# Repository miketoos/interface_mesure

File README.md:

# Projet d'Interface de Mesure pour Calculateur de Voiture

Ce projet vise à développer une interface de mesure entre un calculateur de voiture et l'être humain. L'objectif principal est de gérer jusqu'à 4 signaux d'injection pour une première carte, tandis que pour une deuxième carte, l'interface doit gérer les signaux de PMH (Point Mort Haut), l'écart en degré sur l'avance à l'allumage, le temps de conduction et la valeur d'accélération.

## Configuration du Projet
### Matériel Requis
- Accès à un calculateur de voiture (Clio 2)
- Carte électronique Arduino
- Sonde de programmation JLink
- Port USB B pour le téléversement du code

### Installation des Pilotes
1. Ajoutez la carte via le lien : [https://www.mattairtech.com/software/arduino/package_MattairTech_index.json](https://www.mattairtech.com/software/arduino/package_MattairTech_index.json)
2. Installez la carte via Outils / Type de carte / Gestionnaire de carte
3. Recherchez "MattairTech SAMD|L|C core for Arduino" et installez-le

### Programmation de la Carte
1. Sélectionnez la carte dans Arduino : Outils / Type de carte / "MattairTech MT-D21E(rev B)"
2. Sélectionnez l'oscillateur interne et le port de communication

### Blink (Test de Programmation)
- Assurez-vous que la carte est détectée dans le logiciel Arduino
- Chargez le programme Blink pour tester la programmation

## Fonctionnalités Principales
### Injection
- Contrôle jusqu'à 4 signaux d'injection pour la première carte (à compléter)

### Régime Moteur
- Mesure et affichage du régime moteur en tr/min

### Avance à l'Allumage
- Calcul et contrôle de l'avance à l'allumage en degrés

### Temps de Conduction
- Mesure du temps de conduction du moteur

### Accélération
- Calcul de l'accélération en fonction du régime moteur

## Production et Commande
- Les fichiers Gerber dans la section hardware permettent la production de cartes électroniques. Les entreprises peuvent être contactées en fournissant ces fichiers.
- Les fichiers de la section mécanique facilitent la production de boîtiers pour les cartes électroniques.

## Téléversement du Code
- Les codes nécessaires sont disponibles dans la section software.
- Utilisez une connectique en port USB B pour téléverser le code sur la carte.

## Contribuer
1. Fork le projet
2. Créez une branche pour votre fonctionnalité (`git checkout -b fonctionnalite/nouvelle-fonction`)
3. Committez vos changements (`git commit -m 'Ajout de nouvelle fonctionnalité'`)
4. Push vers la branche (`git push origin fonctionnalite/nouvelle-fonction`)
5. Créez une Pull Request

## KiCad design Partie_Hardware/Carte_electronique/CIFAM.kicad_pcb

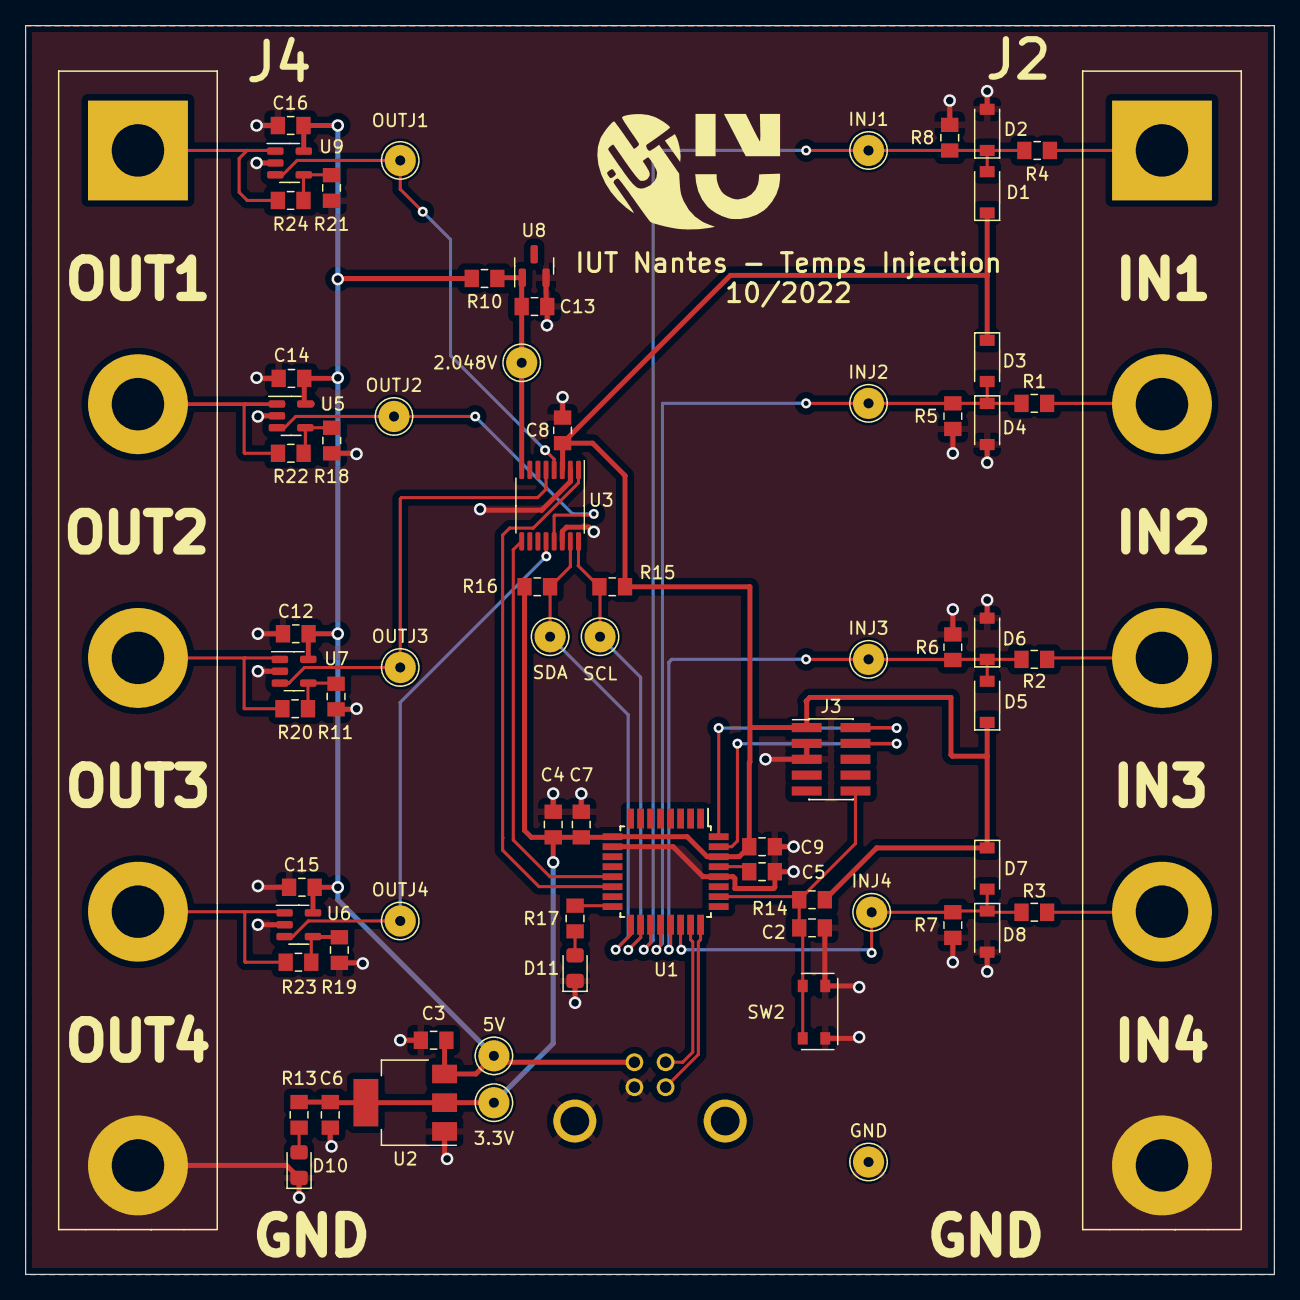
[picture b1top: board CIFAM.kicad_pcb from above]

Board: 2 copper layers, 100.0 x 100.0 mm, 72 parts (0 on the bottom side), 37 nets.

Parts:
2.048V, 3.3V, 5V: TestPoint; TestPoint-12
C2, C5, C7, C8, C9, C12, C14, C15, C16: 100n; C_0805_2012Metric_Pad1.15x1.40mm_HandSolder
C3, C4, C6: 10u; C_0805_2012Metric_Pad1.15x1.40mm_HandSolder
C13: 10n; C_0805_2012Metric_Pad1.15x1.40mm_HandSolder
D1, D2, D3, D4, D5, D6, D7, D8: BAT43W-V; D_SOD-123
D10, D11: LED; LED_0805_2012Metric_Pad1.15x1.40mm_HandSolder
GND: TestPoint; TestPoint-12
INJ1, INJ2, INJ3, INJ4: TestPoint; TestPoint-12
J1: USB_B; USBBSRA
J2, J4: Conn_01x05; Connector_1x05_P2.54mm_Vertical
J3: Conn_02x05_Odd_Even; PinHeader_2x05_P1.27mm_Vertical_SMD
OUTJ1, OUTJ2, OUTJ3, OUTJ4: TestPoint; TestPoint-12
R1, R2, R3, R4: 100k; R_0805_2012Metric_Pad1.15x1.40mm_HandSolder
R5, R6, R7, R8: 39k; R_0805_2012Metric_Pad1.15x1.40mm_HandSolder
R10, R13, R17: 330; R_0805_2012Metric_Pad1.15x1.40mm_HandSolder
R11, R18, R19, R20, R21, R22, R23, R24: 10k; R_0805_2012Metric_Pad1.15x1.40mm_HandSolder
R14: 100K; R_0805_2012Metric_Pad1.15x1.40mm_HandSolder
R15, R16: 4.6k; R_0805_2012Metric_Pad1.15x1.40mm_HandSolder
SCL: TestPoint; TestPoint-12
SDA: TestPoint; TestPoint-12
SW2: SW_Push; Switch_bouton
U1: ATSAMD21E18A-AU; TQFP-32_7x7mm_P0.8mm
U2: LD1117S33TR_SOT223; SOT-223-3_TabPin2
U3: DAC7578xPW; TSSOP-16_4.4x5mm_P0.65mm
U5, U6, U7, U9: MCP6L91T-EOT; SOT-23-5
U8: LM4040DBZ-4.1; SOT-23

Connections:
+3.3V: 3.3V.1, C4.1, C6.1, C7.1, C8.2, C9.1, D1.1 (K), D3.1 (K), D5.1 (K), D7.1 (K), J3.1, R13.1, R14.1, R15.1, R16.2, U1.9 (VDDANA), U1.30 (VDDIN), U2.2 (VO), U3.3 (AVDD)
/+2.048: 2.048V.1, C13.1, R10.1, U3.8 (VREFIN), U8.1 (K)
/CLR: U1.13 (PA10), U3.9 (~CLR)
/IN1: J2.1, R4.1
/IN2: J2.2, R1.1
/IN3: J2.3, R2.1
/IN4: J2.4, R3.1
/INJ1: D1.2 (A), D2.1 (K), INJ1.1, R4.2, R8.1, U1.19 (PA18)
/INJ2: D3.2 (A), D4.1 (K), INJ2.1, R1.2, R5.1, U1.20 (PA19)
/INJ3: D5.2 (A), D6.1 (K), INJ3.1, R2.2, R6.1, U1.21 (PA22)
/INJ4: D7.2 (A), D8.1 (K), INJ4.1, R3.2, R7.1, U1.22 (PA23)
/LDAC: U1.14 (PA11), U3.1 (~LDAC)
/NRST: C2.1, J3.10, R14.2, SW2.1, U1.26 (~RESET)
/OUT1: J4.1, R24.2, U9.1
/OUT2: J4.2, R22.2, U5.1
/OUT3: J4.3, R20.2, U7.1
/OUT4: J4.4, R23.2, U6.1
/OUTJ1: OUTJ1.1, U3.4 (VOUTA), U9.3 (+)
/OUTJ2: OUTJ2.1, U3.13 (VOUTB), U5.3 (+)
/OUTJ3: OUTJ3.1, U3.5 (VOUTC), U7.3 (+)
/OUTJ4: OUTJ4.1, U3.12 (VOUTD), U6.3 (+)
/SCL: R15.2, SCL.1, U1.18 (PA17), U3.16 (SCL)
/SDA: R16.1, SDA.1, U1.17 (PA16), U3.15 (SDA)
/SWCLK: J3.4, U1.31 (PA30)
/SWDIO: J3.2, U1.32 (PA31)
/USB+: J1.3 (D+), U1.24 (PA25)
/USB-: J1.2 (D-), U1.23 (PA24)
GND: C2.2, C3.2, C4.2, C5.2, C6.2, C7.2, C8.1, C9.2, C12.2, C13.2, C14.2, C15.2, C16.2, D2.2 (A), D4.2 (A), D6.2 (A), D8.2 (A), D10.1 (K), D11.1 (K), GND.1, J1.4 (GND), J1.5 (Shield), J2.5, J3.3, J3.5, J4.5, R5.2, R6.2, R7.2, R8.2, R11.2, R18.2, R19.2, R21.2, SW2.2, U1.10 (GND), U1.28 (GND), U2.1 (GND), U3.2 (ADDR0), U3.14 (GND), U5.2 (V-), U6.2 (V-), U7.2 (V-), U8.2 (A), U9.2 (V-)
unnamed: C5.1, U1.29 (VDDCORE)
unnamed: D10.2 (A), R13.2
unnamed: D11.2 (A), R17.2
unnamed: R11.1, R20.1, U7.4 (-)
unnamed: R17.1, U1.16 (PA15)
unnamed: R18.1, R22.1, U5.4 (-)
unnamed: R19.1, R23.1, U6.4 (-)
unnamed: R21.1, R24.1, U9.4 (-)
VBUS: 5V.1, C3.1, C12.1, C14.1, C15.1, C16.1, J1.1 (VBUS), R10.2, U2.3 (VI), U5.5 (V+), U6.5 (V+), U7.5 (V+), U9.5 (V+)

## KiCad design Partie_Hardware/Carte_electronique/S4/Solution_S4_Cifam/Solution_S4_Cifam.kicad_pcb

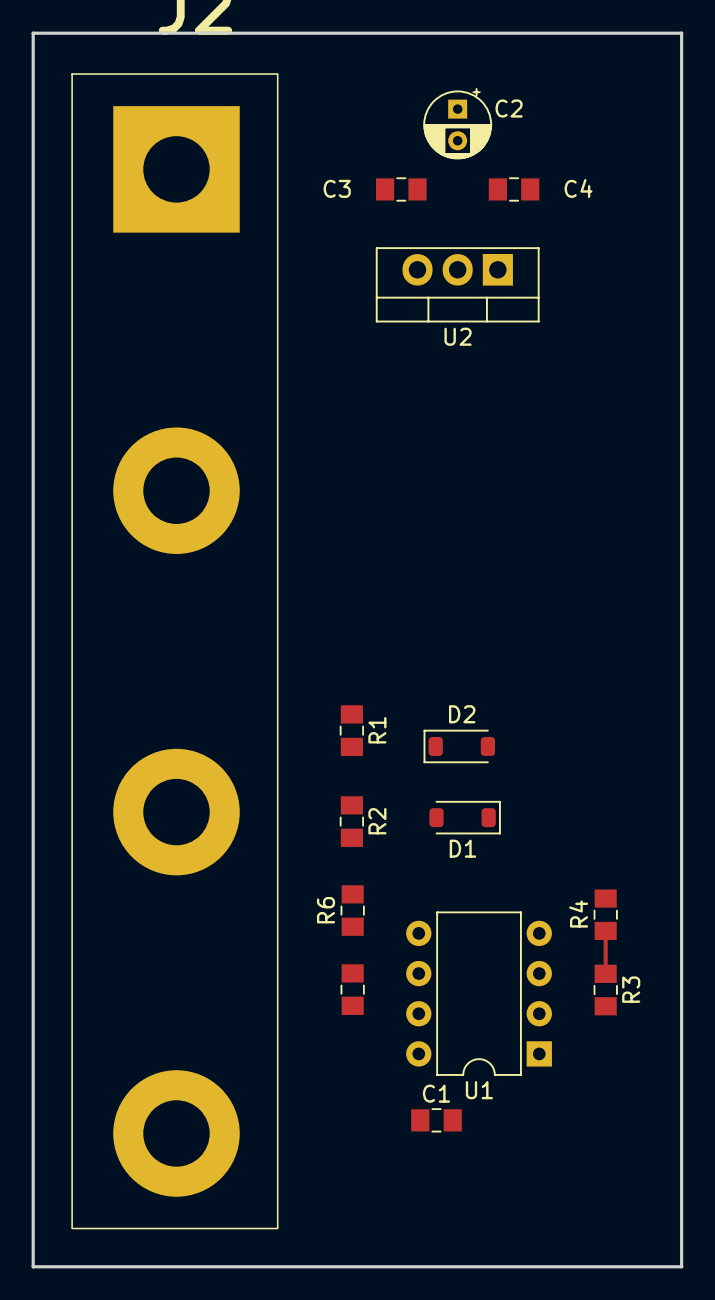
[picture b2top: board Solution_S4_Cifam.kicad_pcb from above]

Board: 2 copper layers, 41.0 x 78.0 mm, 15 parts (0 on the bottom side), 8 nets.

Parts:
C1: 100nF; C_0805_2012Metric_Pad1.15x1.40mm_HandSolder
C2: 10uF; CP_Radial_D4.0mm_P2.00mm
C3, C4: 330nF; C_0805_2012Metric_Pad1.15x1.40mm_HandSolder
D1, D2: BAT43W-V; D_SOD-123
J2: Conn_01x04; Connector_1x04_P2.54mm_Vertical
R1: 100k; R_0805_2012Metric_Pad1.15x1.40mm_HandSolder
R2: 39k; R_0805_2012Metric_Pad1.15x1.40mm_HandSolder
R3, R5: 10k; R_0805_2012Metric_Pad1.15x1.40mm_HandSolder
R4: 5700; R_0805_2012Metric_Pad1.15x1.40mm_HandSolder
R6: 17.5K; R_0805_2012Metric_Pad1.15x1.40mm_HandSolder
U1: LM393; DIP-8_W7.62mm
U2: LF33_TO220; TO-220-3_Vertical

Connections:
+3.3V: C1.1, C4.2, D1.1 (K), R3.2, R5.2, U1.8 (V+), U2.3 (VO)
/IN: C2.1, C3.2, J2.1, R1.1, U2.1 (VI)
/OUT1: J2.2, U1.1
/OUT2: J2.3, U1.7
GND: C1.2, C2.2, C3.1, C4.1, D2.2 (A), J2.4, R2.2, R4.2, R6.2, U1.4 (V-), U2.2 (GND)
unnamed: D1.2 (A), D2.1 (K), R1.2, R2.1, U1.2 (-), U1.5 (+)
unnamed: R3.1, R4.1, U1.3 (+)
unnamed: R5.1, R6.1, U1.6 (-)

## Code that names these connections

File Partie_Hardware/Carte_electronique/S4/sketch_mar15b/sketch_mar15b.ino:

// Code Banc de Test CIFAM : Projet Janvier - Juin 2023 //

// Librairies
#include <Arduino.h>
#include <Wire.h>

// Addresses DAC
#define Adress_dac 0x48 // Adresse du DAC 
#define INJ1 0x30  // Adresse DAC sorti 1
#define INJ2 0x31 // Adresse DAC sorti 2
#define INJ3 0x32 // Adresse DAC sorti 3
#define INJ4 0x33 // Adresse DAC sorti 4
#define INJ5 0x34  // Adresse DAC sorti 5
#define INJ6 0x35 // Adresse DAC sorti 6


// Pin DAC
#define LCLEAR 6
#define LDAC 12

// Led
#define Led 13

// Fonction 
void DacInit();
void DacWrite(unsigned int data, unsigned int channel); 
void GenePW(unsigned int channel, unsigned int EtatBas);
void GeneSignal(unsigned int channel, unsigned int EtatBas, unsigned int EtatHaut);


void setup() 
{
 Serial.begin(9600);
 Serial.println("Serial ok");
 Wire.begin();
 Serial.println("Wire ok");
 DacInit();
 Serial.println("DAC ok");
 pinMode(Led, OUTPUT);
 pinMode(LCLEAR, OUTPUT);
 pinMode(LDAC, OUTPUT);
 digitalWrite(Led, HIGH);
 Serial.println("Setup ok");
}

void loop() 
{
  int Periode = 130000; //µs
  int Temps = 43000; //µs -> Dephasage
  GenePW(INJ2, 100); // Channel, Temps EtatBas
  delayMicroseconds(250); 
  GeneSignal(INJ4, 6000, 1000); // Channel, EtatBas, EtatHaut
  delayMicroseconds(Temps);
  GeneSignal(INJ4, 6000, 1000); // Channel, EtatBas, EtatHaut
  delayMicroseconds(Temps);  
}

void GenePW(unsigned int channel, unsigned int EtatBas)
{
  DacWrite(0, channel);
  delayMicroseconds(EtatBas);
  DacWrite(4000,channel);
}

void GeneSignal(unsigned int channel, unsigned int EtatBas, unsigned int EtatHaut)
{
  DacWrite(0, channel);
  delayMicroseconds(EtatBas);
  DacWrite(4000,channel);
  delayMicroseconds(EtatHaut);
  DacWrite(2000,channel);
}

void DacInit()  // Fonction initialisation DAC
{
  pinMode(LCLEAR, OUTPUT);      // Clear en sortie du DAC
  pinMode(LDAC, OUTPUT);      // Ldac en sortie du DAC
  digitalWrite(LCLEAR, LOW);    // Clear à 0
  digitalWrite(LDAC, LOW);    // Ldac à 0
  digitalWrite(LCLEAR, HIGH);   // Remise à 0 du DAC
}

void DacWrite(unsigned int data, unsigned int channel)
{
  int MSBD, LSBD;       // Variable bit de start et stop

  MSBD = (data & 0xFF0) >> 4;           // 8 bits de poids fort
  LSBD = ((data & 0x00F) << 4 ) & 0x0FF;// 8 bits de poids faible

  Wire.beginTransmission(Adress_dac);   // Commence la transmission sur l'adresse du DAC
  Wire.write(channel);                  // Commence la transmission sur la sortie
  Wire.write(MSBD);                     // On envoie 8 bits de poids forts
  Wire.write(LSBD);                     // On envoie 8 bits de poids faible
  Wire.endTransmission();               // On termine la transmission
}

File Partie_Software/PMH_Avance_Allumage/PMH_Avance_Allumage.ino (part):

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#define Gain_Out4 1  // -> Acceleration : 1V pour 1000(tour/min)−2

#define Address_dac 0x48 // Adresse du DAC
#define OUT1 0x30        // Adresse DAC sortie 1
#define OUT2 0x31        // Adresse DAC sortie 2
#define OUT3 0x32        // Adresse DAC sortie 3
#define OUT4 0x33        // Adresse DAC sortie 4

#define IN1 18 // Pin entrée 1
#define IN2 19 // Pin entrée 2
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void DacInit() // Fonction initialisation DAC
{
  pinMode(10, OUTPUT);    // Clear en sortie du DAC
  pinMode(11, OUTPUT);    // Ldac en sortie du DAC
  digitalWrite(10, LOW);  // Clear à 0
  digitalWrite(11, LOW);  // Ldac à 0
  digitalWrite(10, HIGH); // Remise à 0 du DAC
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
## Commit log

2024-03-04 ajout projet
